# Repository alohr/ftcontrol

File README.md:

ftcontrol
=========

Infrared remote control decoder for fischertechnik car

ATmega328p Timers
=================

TIMER 0
TIMER 1
TIMER 2

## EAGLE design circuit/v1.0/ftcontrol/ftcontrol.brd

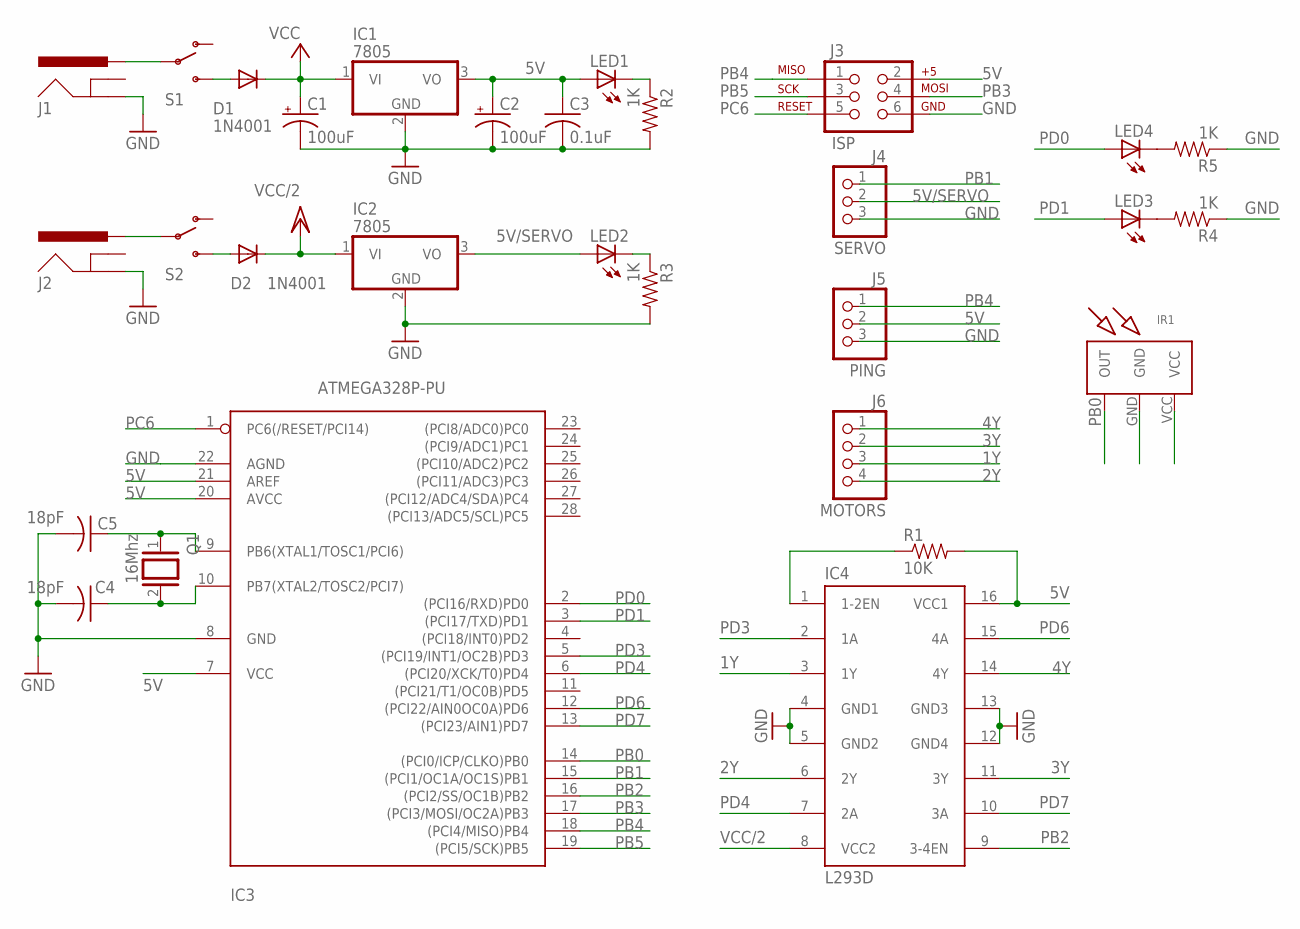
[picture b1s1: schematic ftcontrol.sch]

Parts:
C1: 100uF; CPOL-RADIAL-100UF-25V
C2: 100uF; CPOL-RADIAL-10UF-25V
C3: 0.1uF; C025-025X050
C4, C5: 18pF; C025-025X050
D1, D2: 1N4001; DIODE-1N4001
IC1, IC2: 7805; TO220V
IC3: ATMEGA328P-PU; DIL28-3
IC4: L293D; DIL16
IR1: IR_TSOP4838; TSOP_4838
J1, J2: POWER_JACKPTH; POWER_JACK_PTH
J3: ISP; 2X3
J4: SERVO; 1X03
J5: PING; 1X03
J6: MOTORS; 1X04
LED1, LED2, LED3, LED4: LED3MM
Q1: 16Mhz; QS
R1: 10K; AXIAL-0.4
R2, R3, R4, R5: 1K; AXIAL-0.4
S1, S2: SWITCH-SPDTPTH; SWITCH-SPDT

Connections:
1Y: IC4.3 (1Y), J6.3
2Y: IC4.6 (2Y), J6.4
3Y: IC4.11 (3Y), J6.2
4Y: IC4.14 (4Y), J6.1
5V: C2.1 (+), C3.1, IC1.3 (VO), IC3.7 (VCC), IC3.20 (AVCC), IC3.21 (AREF), IC4.16 (VCC1), IR1.VCC, J3.2, J5.2, LED1.A, R1.P$2 (2)
5V/SERVO: IC2.3 (VO), J4.2, LED2.A
GND: C1.2 (-), C2.2 (-), C3.2, C4.2, C5.2, IC1.2 (GND), IC2.2 (GND), IC3.8 (GND), IC3.22 (AGND), IC4.4 (GND1), IC4.5 (GND2), IC4.12 (GND4), IC4.13 (GND3), IR1.GND, J1.GND, J2.GND, J3.6, J4.3, J5.3, R2.P$2 (2), R3.P$2 (2), R4.P$1 (1), R5.P$1 (1)
unnamed: LED1.K (C), R2.P$1 (1)
unnamed: D1.A, S1.3 (S)
unnamed: LED3.K (C), R4.P$2 (2)
unnamed: J2.PWR, S2.2
unnamed: IC4.1 (1-2EN), R1.P$1 (1)
unnamed: LED2.K (C), R3.P$1 (1)
unnamed: D2.A, S2.3 (S)
unnamed: LED4.K (C), R5.P$2 (2)
unnamed: C5.1, IC3.9 (PB6(XTAL1/TOSC1/PCI6)), Q1.1
unnamed: C4.1, IC3.10 (PB7(XTAL2/TOSC2/PCI7)), Q1.2
unnamed: J1.PWR, S1.2
PB0: IC3.14 ((PCI0/ICP/CLKO)PB0), IR1.OUT
PB1: IC3.15 ((PCI1/OC1A/OC1S)PB1), J4.1
PB2: IC3.16 ((PCI2/SS/OC1B)PB2), IC4.9 (3-4EN)
PB3: IC3.17 ((PCI3/MOSI/OC2A)PB3), J3.4
PB4: IC3.18 ((PCI4/MISO)PB4), J3.1, J5.1
PB5: IC3.19 ((PCI5/SCK)PB5), J3.3
PC6: IC3.1 (PC6(/RESET/PCI14)), J3.5
PD0: IC3.2 ((PCI16/RXD)PD0), LED4.A
PD1: IC3.3 ((PCI17/TXD)PD1), LED3.A
PD3: IC3.5 ((PCI19/INT1/OC2B)PD3), IC4.2 (1A)
PD4: IC3.6 ((PCI20/XCK/T0)PD4), IC4.7 (2A)
PD6: IC3.12 ((PCI22/AIN0OC0A)PD6), IC4.15 (4A)
PD7: IC3.13 ((PCI23/AIN1)PD7), IC4.10 (3A)
VCC: C1.1 (+), D1.C, IC1.1 (VI)
VCC/2: D2.C, IC2.1 (VI), IC4.8 (VCC2)

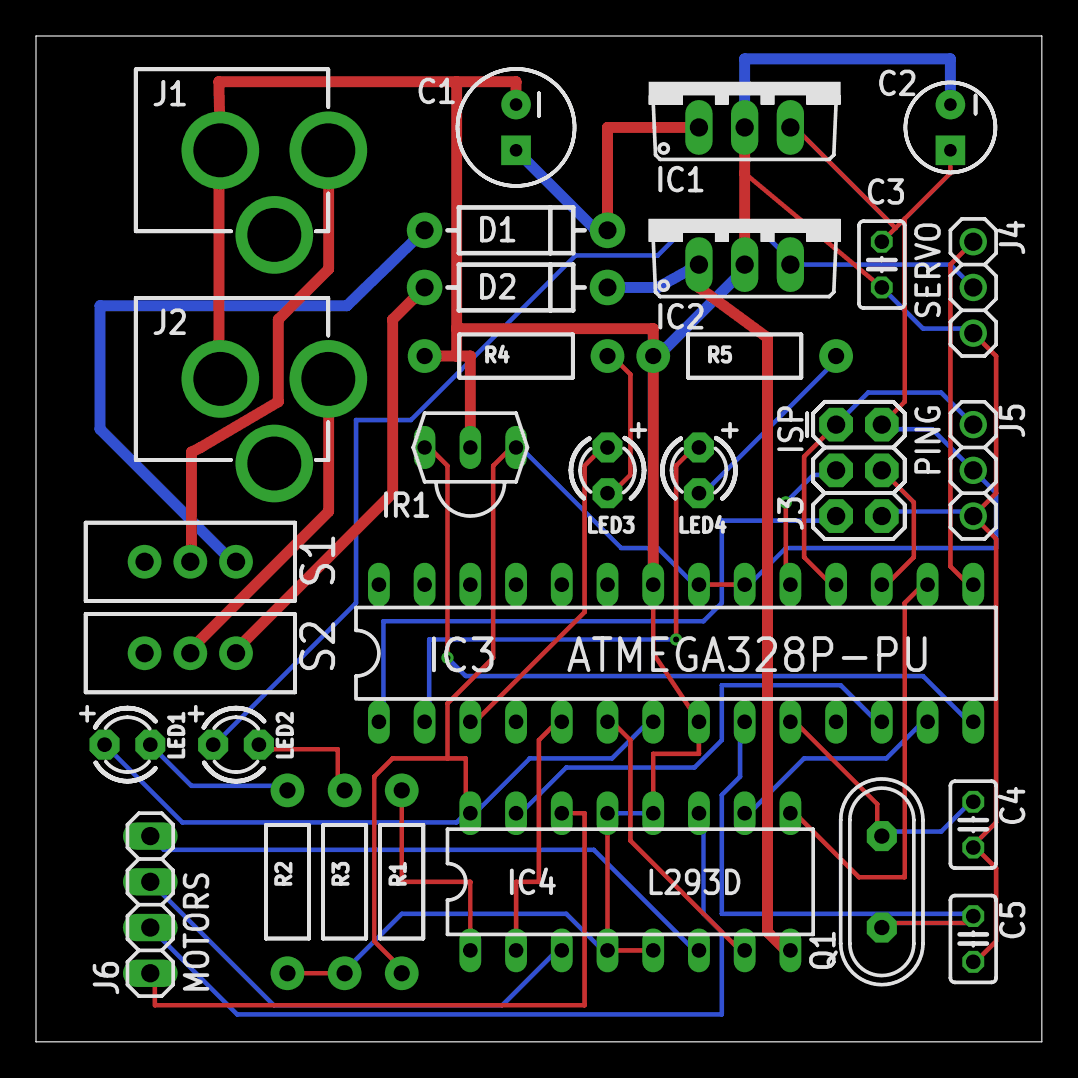
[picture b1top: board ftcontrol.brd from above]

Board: 2 copper layers, 55.9 x 55.9 mm, 30 parts (0 on the bottom side), 33 nets.

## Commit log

2013-08-06 moved servo/ping connectors
2013-08-10 imported firmware

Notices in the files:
parts and their libraries:
SparkFun-Connectors: Licensing: CC v3.0 Share-Alike You are welcome to use this library for commercial purposes.
